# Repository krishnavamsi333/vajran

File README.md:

# Vajran

Robotics Power Distribution & Monitoring Controller

## Overview

Vajran is a protected power distribution and monitoring controller
designed for mobile robots and other embedded robotic platforms.

The project focuses on power distribution, electrical protection,
current and voltage monitoring, and system-level diagnostics.

## Intended Applications

- Mobile robots
- Autonomous robotic platforms
- Distributed actuator systems
- Embedded power management
- Battery-powered machines

## Planned Features

- STM32 microcontroller
- Battery power input
- Protected power distribution
- Multiple switched power outputs
- Voltage monitoring
- Current monitoring
- Temperature monitoring
- Overcurrent protection
- Undervoltage monitoring
- CAN communication
- Status and diagnostic indicators

## Hardware

The PCB is designed using KiCad.

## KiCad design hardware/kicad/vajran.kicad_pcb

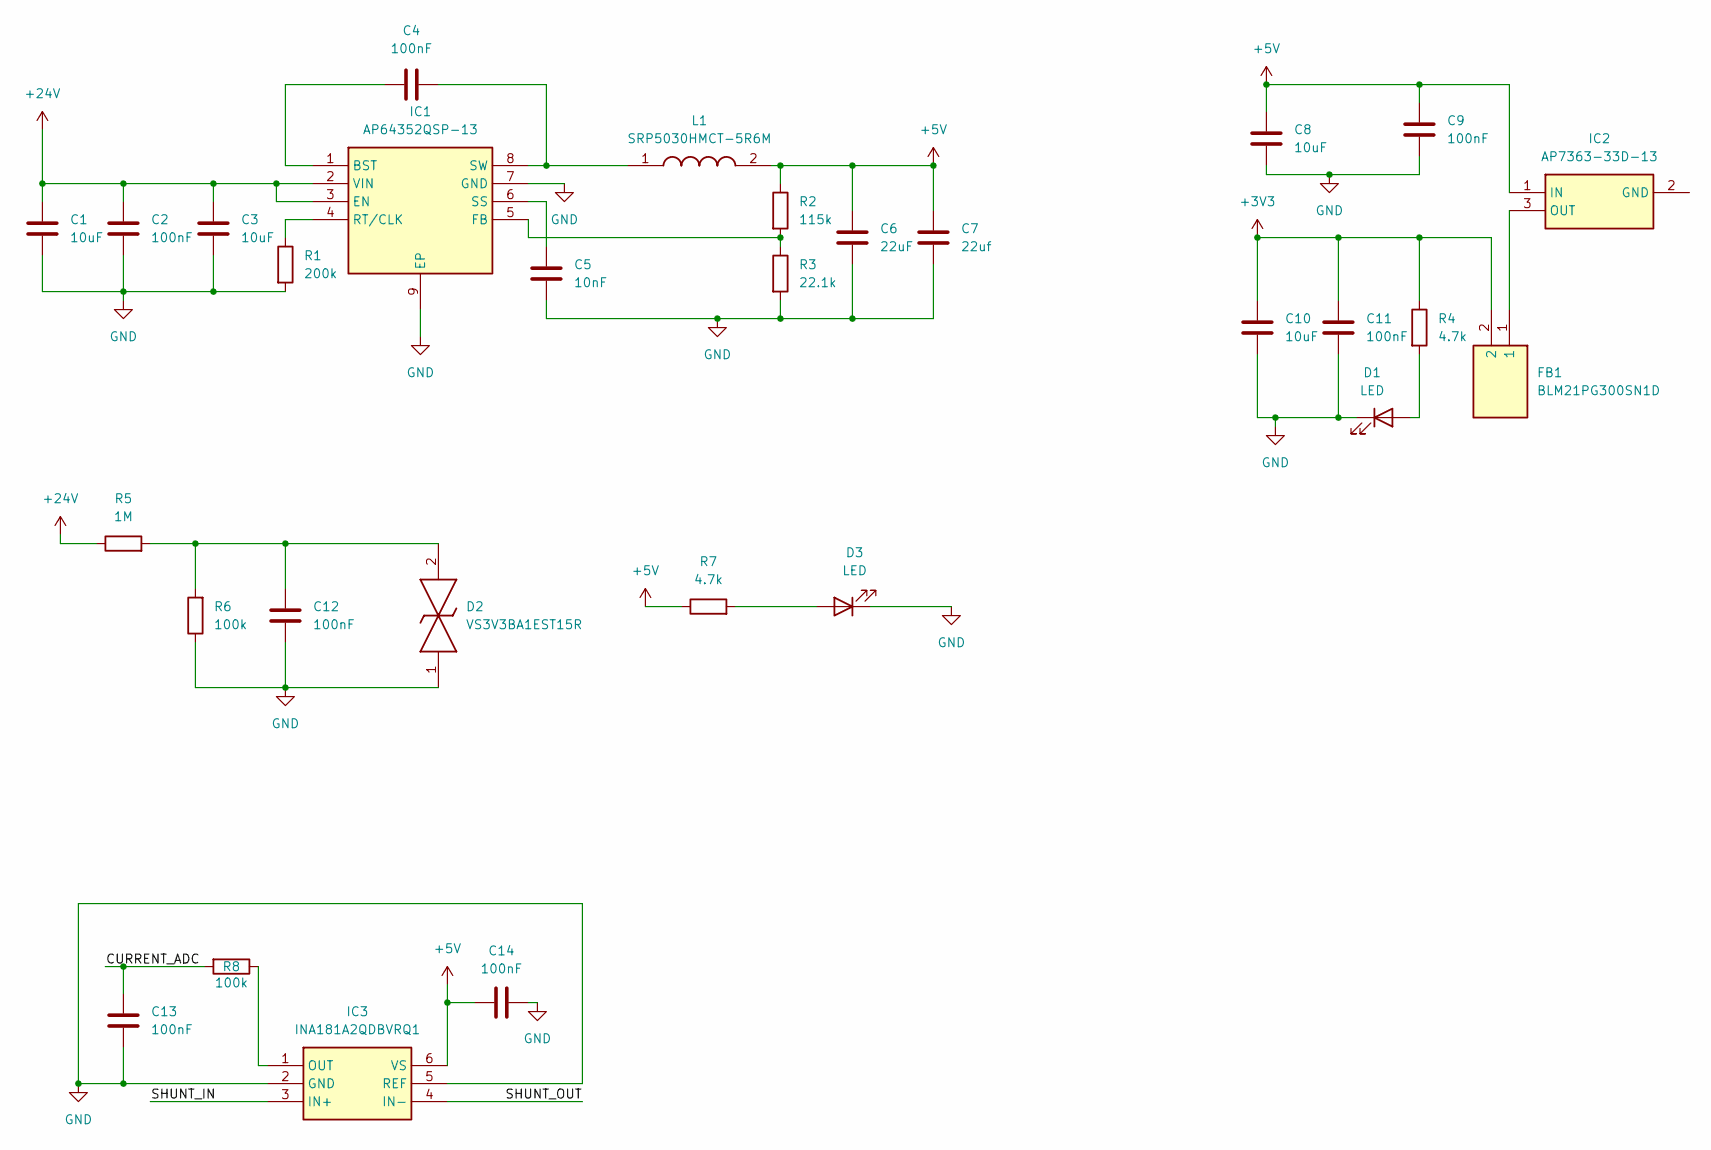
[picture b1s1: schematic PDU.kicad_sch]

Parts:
C1, C3, C8, C10: 10uF; C_0603_1608Metric_Pad1.08x0.95mm_HandSolder
C2, C4, C9, C11, C12, C13, C14: 100nF; C_0603_1608Metric_Pad1.08x0.95mm_HandSolder
C5: 10nF; C_0603_1608Metric_Pad1.08x0.95mm_HandSolder
C6: 22uF; C_0603_1608Metric_Pad1.08x0.95mm_HandSolder
C7: 22uf; C_0603_1608Metric_Pad1.08x0.95mm_HandSolder
D1, D3: LED; LED_0805_2012Metric_Pad1.15x1.40mm_HandSolder
D2: VS3V3BA1EST15R; Manufacturer_Part_Number VS3V3BA1EST15R; Mouser Part Number 755-VS3V3BA1EST15R
FB1: BLM21PG300SN1D; BEADC2012X105N; Manufacturer_Part_Number BLM21PG300SN1D; Mouser Part Number 81-BLM21P300S
IC1: AP64352QSP-13; SOIC127P600X163-9N; Manufacturer_Part_Number AP64352QSP-13; Mouser Part Number 621-AP64352QSP-13
IC2: AP7363-33D-13; AP736333D13; Manufacturer_Part_Number AP7363-33D-13; Mouser Part Number 621-AP7363-33D-13
IC3: INA181A2QDBVRQ1; SOT95P280X145-6N; Manufacturer_Part_Number INA181A2QDBVRQ1; Mouser Part Number 595-INA181A2QDBVRQ1
L1: SRP5030HMCT-5R6M; SRP5030HMCT100M; Manufacturer_Part_Number SRP5030HMCT-5R6M
R1: 200k; R_0603_1608Metric_Pad0.98x0.95mm_HandSolder
R2: 115k; R_0603_1608Metric_Pad0.98x0.95mm_HandSolder
R3: 22.1k; R_0603_1608Metric_Pad0.98x0.95mm_HandSolder
R4, R7: 4.7k; R_0603_1608Metric_Pad0.98x0.95mm_HandSolder
R5: 1M; R_0603_1608Metric_Pad0.98x0.95mm_HandSolder
R6, R8: 100k; R_0603_1608Metric_Pad0.98x0.95mm_HandSolder

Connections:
+3V3: C10.1, C11.2, FB1.2, R4.1; also elsewhere on the board
+5V: C6.1, C7.1, C8.1, C9.2, C14.2, IC2.1 (IN), IC3.6 (VS), L1.2, R2.1, R7.1; also elsewhere on the board
+24V: C1.1, C2.1, C3.1, IC1.2 (VIN), IC1.3 (EN), R5.1
/PDU/CURRENT_ADC: C13.2, R8.2
/PDU/SHUNT_IN: IC3.3 (IN+)
/PDU/SHUNT_OUT: IC3.4 (IN-)
GND: C1.2, C2.2, C3.2, C5.2, C6.2, C7.2, C8.2, C9.1, C10.2, C11.1, C12.2, C13.1, C14.1, D1.1 (K), D2.1, D3.1 (K), IC1.7 (GND), IC1.9 (EP), IC3.2 (GND), IC3.5 (REF), R1.2, R3.2, R6.1; also elsewhere on the board
unnamed: C12.1, D2.2, R5.2, R6.2
unnamed: D1.2 (A), R4.2
unnamed: D3.2 (A), R7.2
unnamed: C4.2, IC1.1 (BST)
unnamed: IC1.5 (FB), R2.2, R3.1
unnamed: IC1.4 (RT/CLK), R1.1
unnamed: C5.1, IC1.6 (SS)
unnamed: C4.1, IC1.8 (SW), L1.1
unnamed: FB1.1, IC2.3 (OUT)
unnamed: IC3.1 (OUT), R8.1

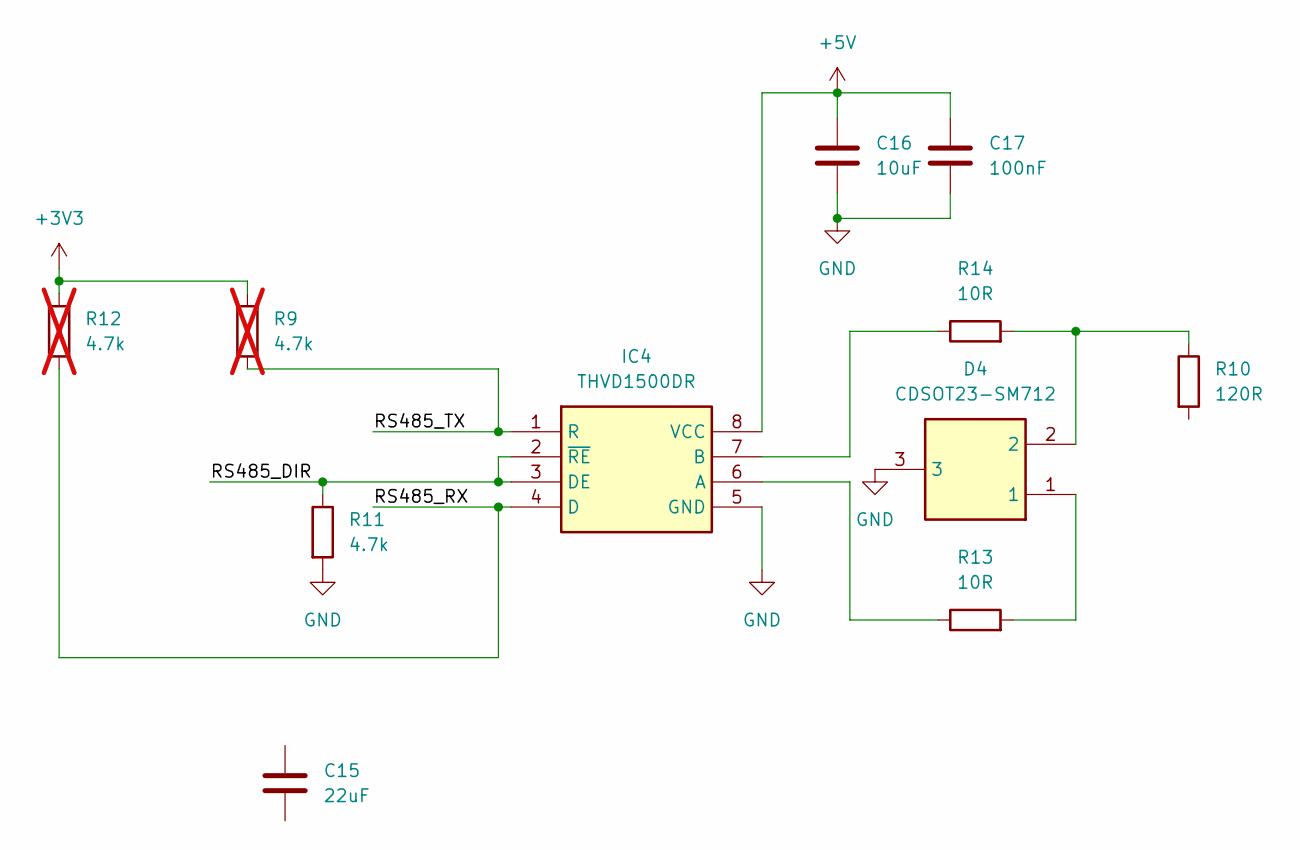
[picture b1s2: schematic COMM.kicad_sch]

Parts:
C15: 22uF; C_0603_1608Metric_Pad1.08x0.95mm_HandSolder
C16: 10uF; C_0603_1608Metric_Pad1.08x0.95mm_HandSolder
C17: 100nF; C_0603_1608Metric_Pad1.08x0.95mm_HandSolder
D4: CDSOT23-SM712; SOT95P230X117-3N; Manufacturer_Part_Number CDSOT23-SM712; Mouser Part Number 652-CDSOT23-SM712
IC4: THVD1500DR; SOIC127P600X175-8N; Manufacturer_Part_Number THVD1500DR; Mouser Part Number 595-THVD1500DR
R9, R12: 4.7k; R_0603_1608Metric_Pad0.98x0.95mm_HandSolder; not fitted
R10: 120R; R_0603_1608Metric_Pad0.98x0.95mm_HandSolder
R11: 4.7k; R_0603_1608Metric_Pad0.98x0.95mm_HandSolder
R13, R14: 10R; R_0603_1608Metric_Pad0.98x0.95mm_HandSolder

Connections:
+3V3: R9.1, R12.1; also elsewhere on the board
+5V: C16.1, C17.2, IC4.8 (VCC); also elsewhere on the board
/COMMUNICATION/RS485_DIR: IC4.2 (~RE), IC4.3 (DE), R11.1
/COMMUNICATION/RS485_RX: IC4.4 (D), R12.2
/COMMUNICATION/RS485_TX: IC4.1 (R), R9.2
GND: C16.2, C17.1, D4.3, IC4.5 (GND), R11.2; also elsewhere on the board
unnamed: D4.1, R13.2
unnamed: D4.2, R10.1, R14.2
unnamed: IC4.6 (A), R13.1
unnamed: IC4.7 (B), R14.1

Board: 4 copper layers, 41 parts (0 on the bottom side), 22 nets, no tracks yet.
